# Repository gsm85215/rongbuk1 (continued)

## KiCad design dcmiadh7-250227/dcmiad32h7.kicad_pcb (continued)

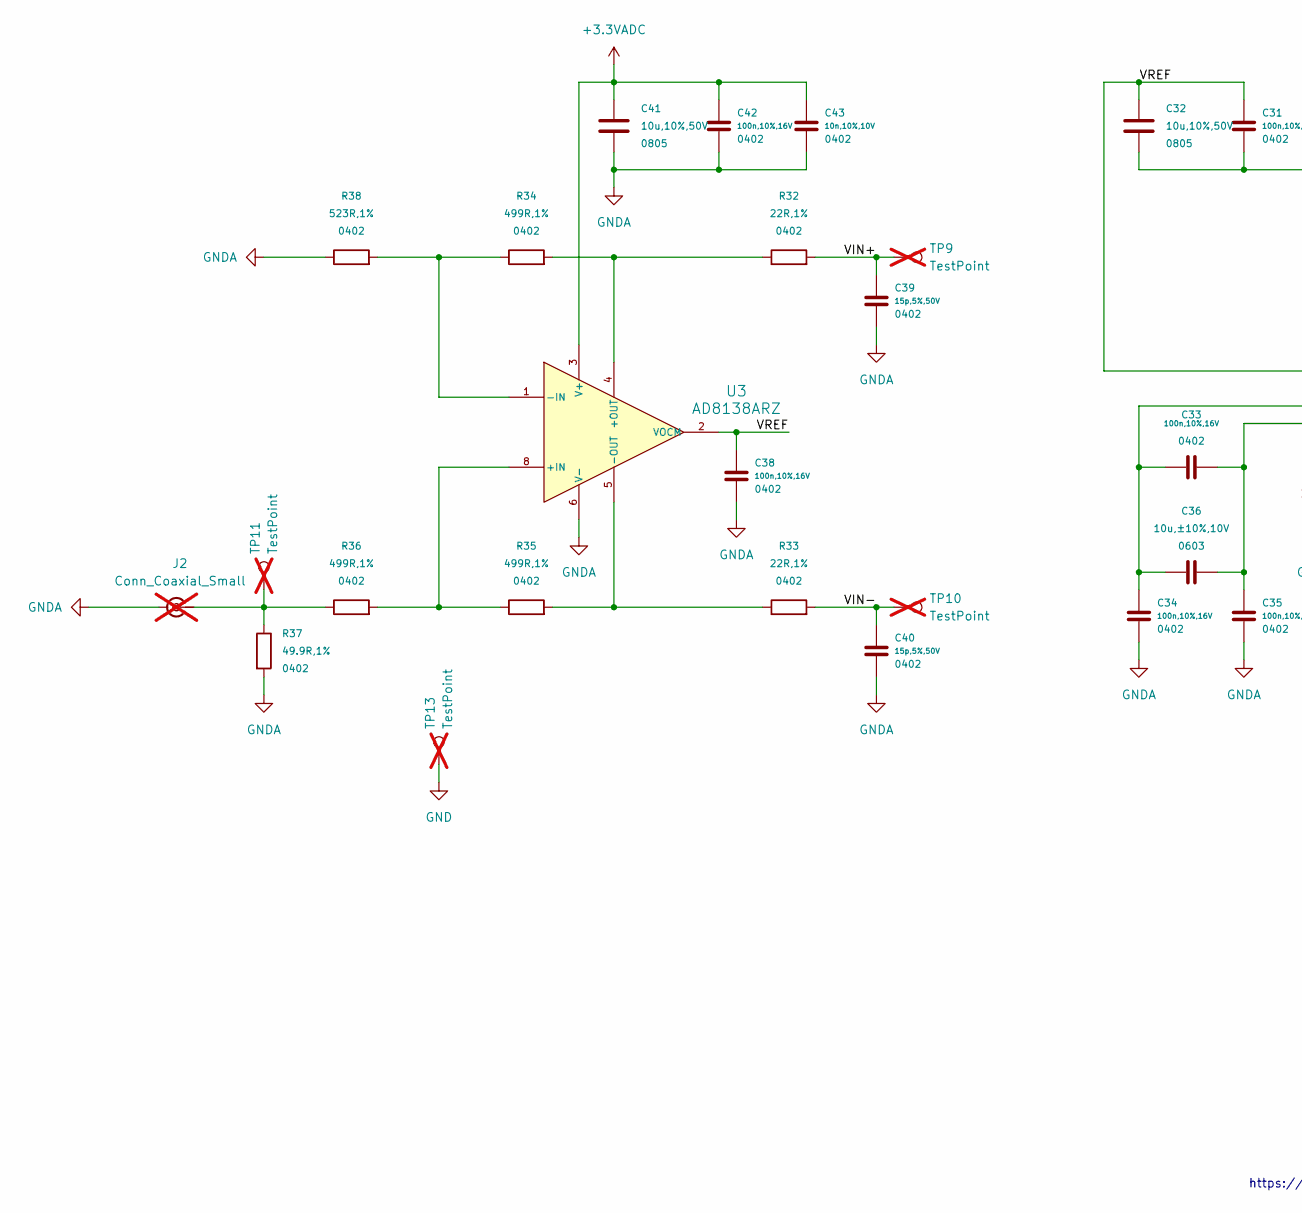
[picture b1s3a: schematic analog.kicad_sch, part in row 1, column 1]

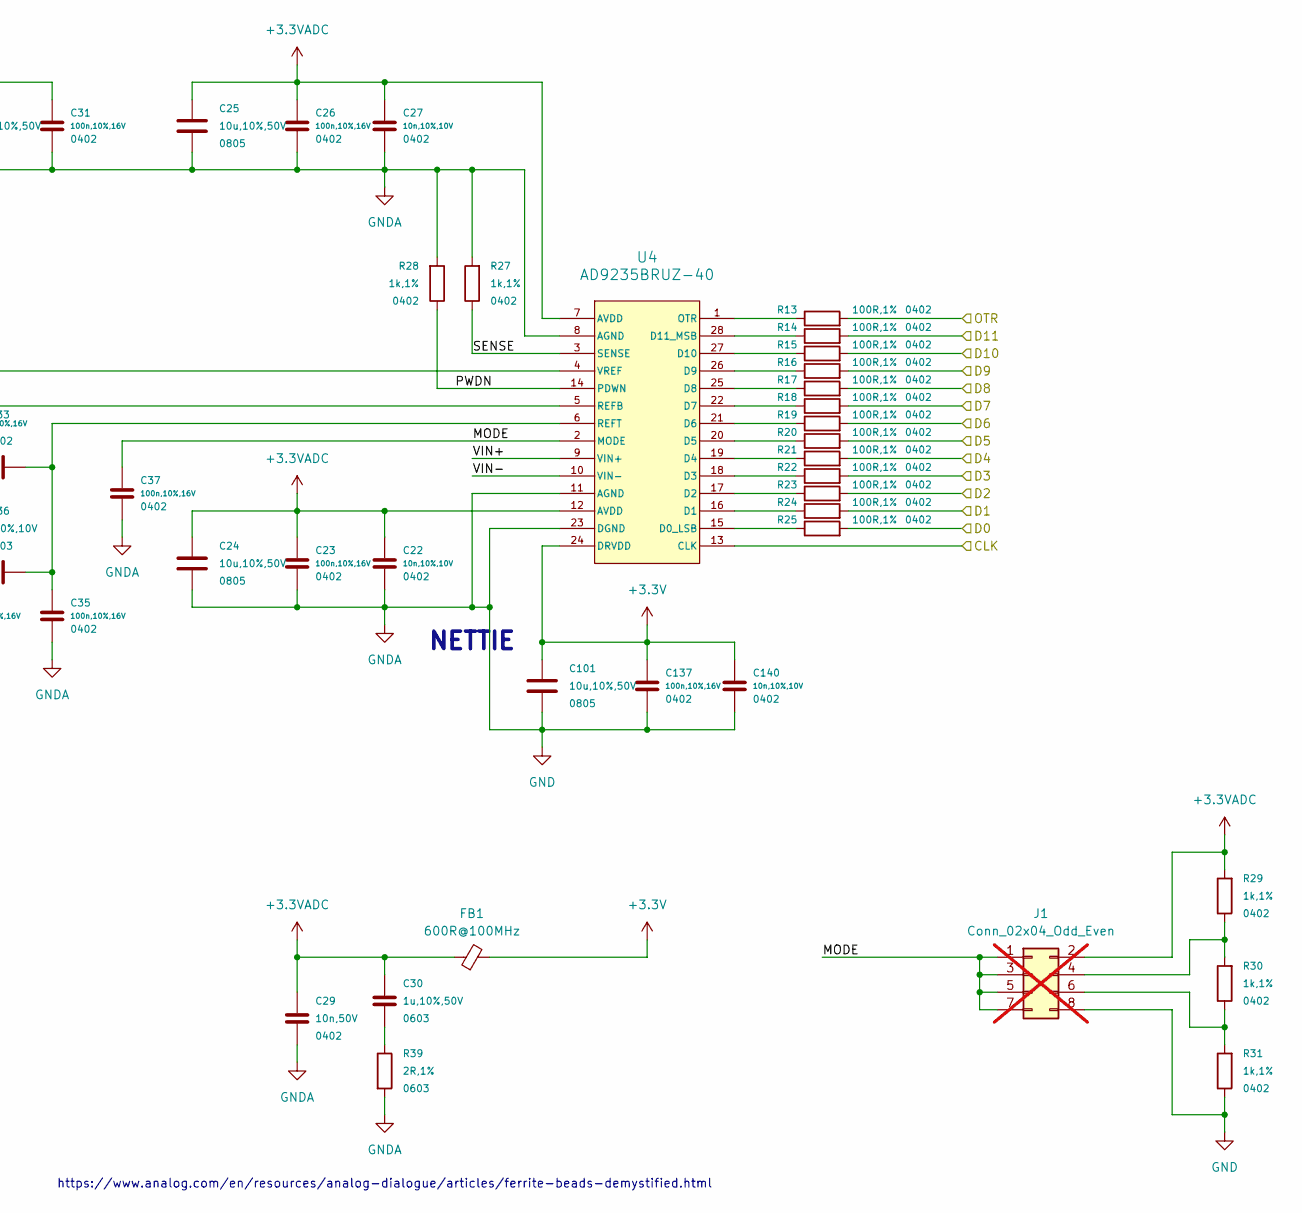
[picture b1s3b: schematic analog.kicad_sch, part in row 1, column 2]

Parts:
C22, C27, C43, C140: 10n,10%,10V; C_0402_1005Metric_for_0.25mm_grid; Manufacturer Part CL05B103KB5NNNC
C23, C26, C31, C33, C34, C35, C37, C38, C42, C137: 100n,10%,16V; C_0402_1005Metric_for_0.25mm_grid; Manufacturer Part CL05B104KO5NNNC
C24, C25, C32, C41, C101: 10u,10%,50V; C_0805_2012Metric; Manufacturer Part GRM21BR61H106KE43L
C29: 10n,50V; C_0402_1005Metric_for_0.25mm_grid; Manufacturer Part CL05B103KB5NNNC
C30: 1u,10%,50V; C_0603_1608Metric_1.28x0.64mm_Courtyard; Manufacturer Part CL10A105KB8NNNC
C36: 10u,±10%,10V; C_0603_1608Metric_1.28x0.64mm_Courtyard; Manufacturer Part CL10A106KP8NNNC
C39, C40: 15p,5%,50V; C_0402_1005Metric_for_0.25mm_grid; Manufacturer Part 0402CG150J500NT
FB1: 600R@100MHz; L_0805_2012Metric; Manufacturer Part GZ2012D601TF
J1: Conn_02x04_Odd_Even; PinHeader_2x04_P2.54mm_Vertical; not fitted
J2: Conn_Coaxial_Small; SMA_Amphenol_901-144_Vertical; not fitted
R13, R14, R15, R16, R17, R18, R19, R20, R21, R22, R23, R24, R25: 100R,1%; R_0402_1005Metric_for_0.25mm_grid; Manufacturer Part 0402WGF1000TCE
R27, R28, R29, R30, R31: 1k,1%; R_0402_1005Metric_for_0.25mm_grid; Manufacturer Part 0402WGF1001TCE
R32, R33: 22R,1%; R_0402_1005Metric_for_0.25mm_grid; Manufacturer Part 0402WGF220JTCE
R34, R35, R36: 499R,1%; R_0402_1005Metric_for_0.25mm_grid; Manufacturer Part RC0402FR-07499RL
R37: 49.9R,1%; R_0402_1005Metric_for_0.25mm_grid; Manufacturer Part 0402WGF499JTCE
R38: 523R,1%; R_0402_1005Metric_for_0.25mm_grid; Manufacturer Part TC0225B5230TCC
R39: 2R,1%; R_0603_1608Metric_1.28x0.64mm_Courtyard; Manufacturer Part 0603WAF200KT5E
TP9, TP10, TP11, TP13: TestPoint; TestPoint_THTPad_D1.0mm_Drill0.5mm; not fitted
U3: AD8138ARZ; SOIC-8_3.9x4.9mm_P1.27mm; Manufacturer Part AD8138ARZ-R7
U4: AD9235BRUZ-40; TSSOP-28_4.4x9.7mm_P0.65mm; Manufacturer Part AD9235BRUZ-40

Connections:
+3.3V: C101.1, C137.1, C140.1, FB1.2, U4.24 (DRVDD); also elsewhere on the board
+3.3VADC: C22.1, C23.1, C24.1, C25.1, C26.1, C27.1, C29.1, C30.1, C41.1, C42.1, C43.1, FB1.1, J1.2, R29.2, U3.3 (V+), U4.7 (AVDD), U4.12 (AVDD)
/analog/CLK: U4.13 (CLK); also elsewhere on the board
/analog/D0: R25.2; also elsewhere on the board
/analog/D1: R24.2; also elsewhere on the board
/analog/D2: R23.2; also elsewhere on the board
/analog/D3: R22.2; also elsewhere on the board
/analog/D4: R21.2; also elsewhere on the board
/analog/D5: R20.2; also elsewhere on the board
/analog/D6: R19.2; also elsewhere on the board
/analog/D7: R18.2; also elsewhere on the board
/analog/D8: R17.2; also elsewhere on the board
/analog/D9: R16.2; also elsewhere on the board
/analog/D10: R15.2; also elsewhere on the board
/analog/D11: R14.2; also elsewhere on the board
/analog/MODE: C37.1, J1.1, J1.3, J1.5, J1.7, U4.2 (MODE)
/analog/OTR: R13.2; also elsewhere on the board
/analog/PWDN: R28.1, U4.14 (PDWN)
/analog/SENSE: R27.1, U4.3 (SENSE)
/analog/VIN+: C39.1, R32.2, TP9.1, U4.9 (VIN+)
/analog/VIN-: C40.1, R33.2, TP10.1, U4.10 (VIN-)
/analog/VREF: C31.1, C32.1, C38.1, U3.2 (VOCM), U4.4 (VREF)
GND: C22.2, C23.2, C24.2, C25.2, C26.2, C27.2, C29.2, C31.2, C32.2, C34.2, C35.2, C37.2, C38.2, C39.2, C40.2, C41.2, C42.2, C43.2, C101.2, C137.2, C140.2, J1.8, J2.2 (Ext), R27.2, R28.2, R31.1, R37.2, R38.1, R39.2, TP13.1, U3.6 (V-), U4.8 (AGND), U4.11 (AGND), U4.23 (DGND); also elsewhere on the board
unnamed: C30.2, R39.1
unnamed: J1.4, R29.1, R30.2
unnamed: J1.6, R30.1, R31.2
unnamed: J2.1 (In), R36.1, R37.1, TP11.1
unnamed: R35.1, R36.2, U3.8 (+IN)
unnamed: R32.1, R34.2, U3.4 (+OUT)
unnamed: R34.1, R38.2, U3.1 (-IN)
unnamed: R33.1, R35.2, U3.5 (-OUT)
unnamed: R25.1, U4.15 (D0_LSB)
unnamed: R24.1, U4.16 (D1)
unnamed: R23.1, U4.17 (D2)
unnamed: R22.1, U4.18 (D3)
unnamed: R21.1, U4.19 (D4)
unnamed: R20.1, U4.20 (D5)
unnamed: R19.1, U4.21 (D6)
unnamed: R18.1, U4.22 (D7)
unnamed: R17.1, U4.25 (D8)
unnamed: R16.1, U4.26 (D9)
unnamed: R15.1, U4.27 (D10)
unnamed: R14.1, U4.28 (D11_MSB)
unnamed: R13.1, U4.1 (OTR)
unnamed: C33.1, C34.1, C36.1, U4.5 (REFB)
unnamed: C33.2, C35.1, C36.2, U4.6 (REFT)

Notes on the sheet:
https://www.analog.com/en/resources/analog-dialogue/articles/ferrite-beads-demystified.html
NETTIE

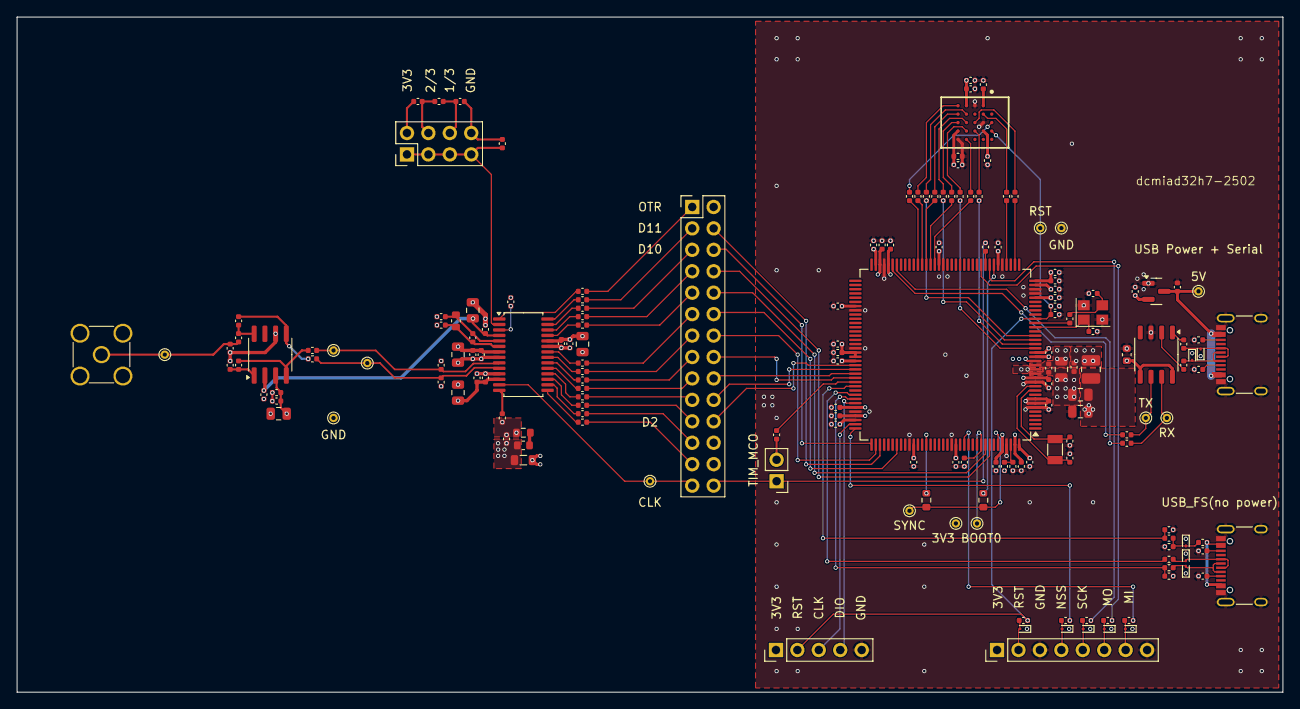
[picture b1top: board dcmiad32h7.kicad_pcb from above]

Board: 4 copper layers, 150.0 x 80.0 mm, 174 parts (0 on the bottom side), 127 nets.

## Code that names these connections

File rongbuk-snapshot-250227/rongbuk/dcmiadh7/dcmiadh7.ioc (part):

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Mcu.Name=STM32H725ZGTx
Mcu.Package=LQFP144
Mcu.UserName=STM32H725ZGTx
PA1.Mode=OCTOSPI1_Port1_DQS
PA1.Signal=OCTOSPIM_P1_DQS
PA11.Mode=Device_Only_FS
PA11.Signal=USB_OTG_HS_DM
PA12.Mode=Device_Only_FS
PA12.Signal=USB_OTG_HS_DP
PA13(JTMS/SWDIO).Mode=Serial_Wire
PA13(JTMS/SWDIO).Signal=DEBUG_JTMS-SWDIO
PA14(JTCK/SWCLK).Mode=Serial_Wire
PA14(JTCK/SWCLK).Signal=DEBUG_JTCK-SWCLK
PA15(JTDI).Mode=NSS_Signal_Hard_Output
PA15(JTDI).Signal=SPI1_NSS
PA3.Mode=O1_P1_CLK
PA3.Signal=OCTOSPIM_P1_CLK
PA4.Mode=Slave_10_bits_External_Synchro
PA4.Signal=DCMI_HSYNC
PA5.Mode=Full_Duplex_Master
PA5.Signal=SPI1_SCK
PA6.Mode=Slave_10_bits_External_Synchro
PA6.Signal=DCMI_PIXCLK
PA7.Mode=Full_Duplex_Master
PA7.Signal=SPI1_MOSI
PA9.Mode=Activate_VBUS_FS
PA9.Signal=USB_OTG_HS_VBUS
PB10.Mode=Asynchronous
PB10.Signal=USART3_TX
PB11.Mode=Asynchronous
PB11.Signal=USART3_RX
PB4(NJTRST).Mode=Full_Duplex_Master
PB4(NJTRST).Signal=SPI1_MISO
PB8.Mode=Slave_10_bits_External_Synchro
PB8.Signal=DCMI_D6
PB9.Mode=Slave_10_bits_External_Synchro
PB9.Signal=DCMI_D7
PC10.Mode=Slave_10_bits_External_Synchro
PC10.Signal=DCMI_D8
PC11.Mode=Slave_10_bits_External_Synchro
PC11.Signal=DCMI_D4
PC12.Mode=Slave_10_bits_External_Synchro
PC12.Signal=DCMI_D9
PC14-OSC32_IN.Mode=LSE-External-Oscillator
PC14-OSC32_IN.Signal=RCC_OSC32_IN
PC15-OSC32_OUT.Mode=LSE-External-Oscillator
PC15-OSC32_OUT.Signal=RCC_OSC32_OUT
PC6.Mode=Slave_10_bits_External_Synchro
PC6.Signal=DCMI_D0
PC7.Mode=Slave_10_bits_External_Synchro
PC7.Signal=DCMI_D1
PC8.Mode=Slave_10_bits_External_Synchro
PC8.Signal=DCMI_D2
PC9.Mode=Slave_10_bits_External_Synchro
PC9.Signal=DCMI_D3
PD3.Mode=Slave_10_bits_External_Synchro
PD3.Signal=DCMI_D5
PE1.GPIOParameters=GPIO_Label
PE1.GPIO_Label=SYNC
PE1.Signal=GPIO_Output
PE10.Mode=OCTOSPI1_IOH_Port1H
PE10.Signal=OCTOSPIM_P1_IO7
PE11.Mode=OCTOSPI1_Port1_NCS
PE11.Signal=OCTOSPIM_P1_NCS
PE7.Mode=OCTOSPI1_IOH_Port1H
PE7.Signal=OCTOSPIM_P1_IO4
PE8.Mode=OCTOSPI1_IOH_Port1H
PE8.Signal=OCTOSPIM_P1_IO5
PE9.Mode=OCTOSPI1_IOH_Port1H
PE9.Signal=OCTOSPIM_P1_IO6
PF6.Mode=OCTOSPI1_IOL_Port1L
PF6.Signal=OCTOSPIM_P1_IO3
PF7.Mode=OCTOSPI1_IOL_Port1L
PF7.Signal=OCTOSPIM_P1_IO2
PF8.Mode=OCTOSPI1_IOL_Port1L
PF8.Signal=OCTOSPIM_P1_IO0
PF9.Mode=OCTOSPI1_IOL_Port1L
PF9.Signal=OCTOSPIM_P1_IO1
PG9.Mode=Slave_10_bits_External_Synchro
PG9.Signal=DCMI_VSYNC
PH0-OSC_IN.Mode=HSE-External-Oscillator
PH0-OSC_IN.Signal=RCC_OSC_IN
PH1-OSC_OUT.Mode=HSE-External-Oscillator
PH1-OSC_OUT.Signal=RCC_OSC_OUT
RCC.HSE_VALUE=25000000
RCC.SYSCLKFreq_VALUE=64000000
board=custom

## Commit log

2025-03-04 mabo
